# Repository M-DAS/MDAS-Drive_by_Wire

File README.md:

# MDAS-Drive_by_Wire
The drive-by-wire division of the University of Michigan-Dearborn Autonomous Shuttle.

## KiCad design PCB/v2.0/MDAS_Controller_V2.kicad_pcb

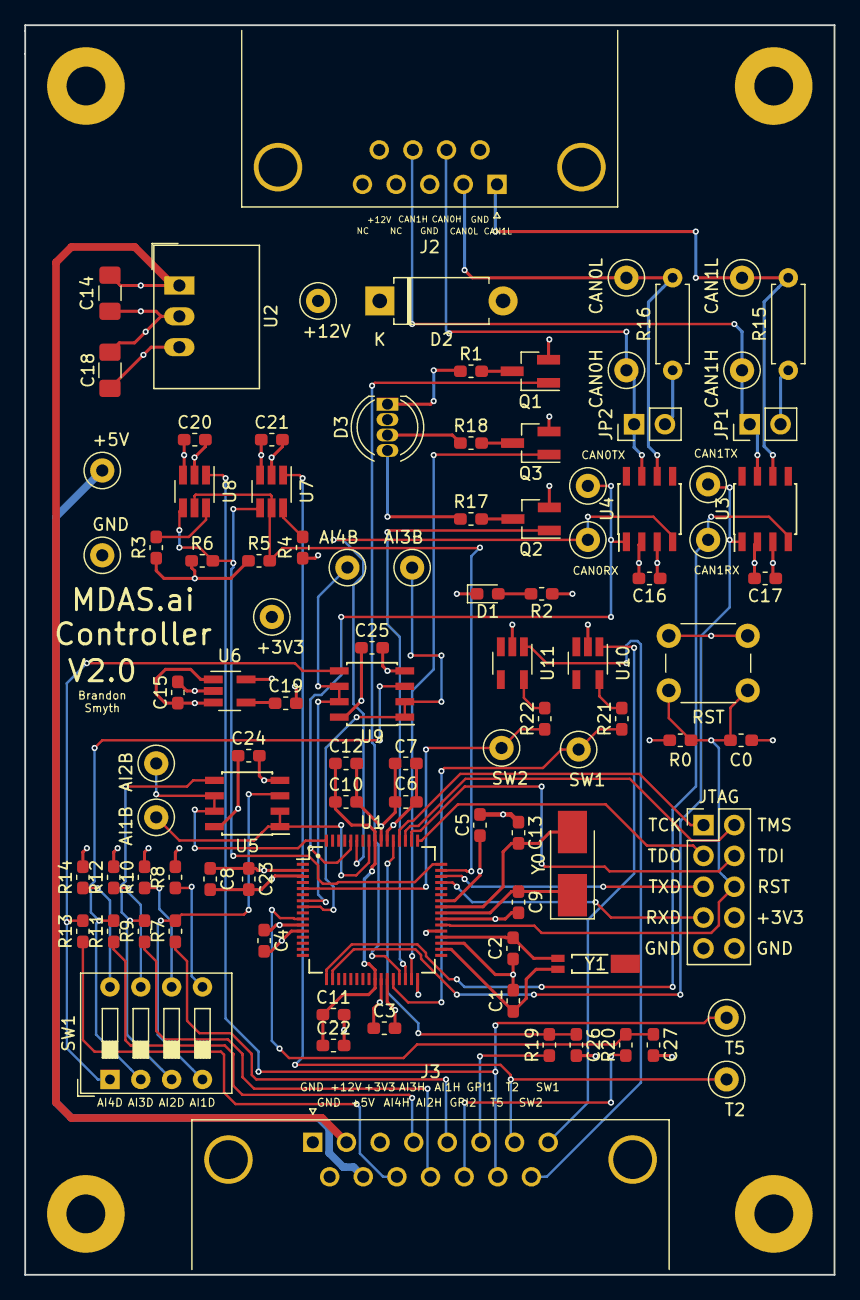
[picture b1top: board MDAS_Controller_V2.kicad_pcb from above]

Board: 4 copper layers, 66.7 x 102.9 mm, 101 parts (0 on the bottom side), 69 nets.

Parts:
+3V3, +5V, +12V: TestPoint; TestPoint_Loop_D1.80mm_Drill1.0mm_Beaded
AI1B, AI2B, AI3B, AI4B: TestPoint; TestPoint_Loop_D1.80mm_Drill1.0mm_Beaded
C0, C3, C4, C5, C6, C10, C11, C16, C17, C20, C21, C24, C25: 0.1uF; C_0603_1608Metric_Pad1.05x0.95mm_HandSolder
C1, C2: 24pF; C_0603_1608Metric_Pad1.05x0.95mm_HandSolder
C7, C22: 2.2uF; C_0603_1608Metric_Pad1.05x0.95mm_HandSolder
C8, C12, C15: 1.0uF; C_0603_1608Metric_Pad1.05x0.95mm_HandSolder
C9, C13: 10pF; C_0603_1608Metric_Pad1.05x0.95mm_HandSolder
C14, C18: 10uF; C_1206_3216Metric_Pad1.42x1.75mm_HandSolder
C19, C23, C26, C27: 0.01uF; C_0603_1608Metric_Pad1.05x0.95mm_HandSolder
CAN0H, CAN0L, CAN0RX, CAN0TX, CAN1H, CAN1L, CAN1RX, CAN1TX: TestPoint; TestPoint_Loop_D1.80mm_Drill1.0mm_Beaded
D1: LED; LED_0603_1608Metric_Pad1.05x0.95mm_HandSolder
D2: TP6KE33A; D_DO-15_P10.16mm_Horizontal
D3: LED_RABG; LED_D5.0mm-4
GND: TestPoint; TestPoint_Loop_D1.80mm_Drill1.0mm_Beaded
J2: DB9_Male; DSUB-9_Male_Horizontal_P2.77x2.84mm_EdgePinOffset9.90mm_Hou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
J3: DB15_Male; DSUB-15_Male_Horizontal_P2.77x2.84mm_EdgePinOffset7.70mm_Ho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
JP1, JP2: Jumper_NC_Small; PinHeader_1x02_P2.54mm_Vertical
JTAG: JTAG; PinHeader_2x05_P2.54mm_Vertical
MH1, MH2, MH3, MH4: MountingHole_Pad; MountingHole_3.2mm_M3_Pad
Q1, Q2, Q3: DTC114E; SOT-23_Handsoldering
R0, R3, R4, R5, R6: 10k; R_0603_1608Metric_Pad1.05x0.95mm_HandSolder
R1, R2, R17, R18: 330; R_0603_1608Metric_Pad1.05x0.95mm_HandSolder
R7, R9, R11, R13: 11k; R_0603_1608Metric_Pad1.05x0.95mm_HandSolder
R8, R10, R12, R14: 21k; R_0603_1608Metric_Pad1.05x0.95mm_HandSolder
R15, R16: 120; R_Axial_DIN0207_L6.3mm_D2.5mm_P7.62mm_Horizontal
R19, R20, R21, R22: 1k; R_0603_1608Metric_Pad1.05x0.95mm_HandSolder
RST: SW_Push; SW_PUSH_6mm_H5mm
SW1: SW_DIP_x04; SW_DIP_SPSTx04_Slide_9.78x12.34mm_W7.62mm_P2.54mm
SW1#2, SW2: TestPoint; TestPoint_Loop_D1.80mm_Drill1.0mm_Beaded
T2, T5: TestPoint; TestPoint_Loop_D1.80mm_Drill1.0mm_Beaded
U1: TM4C123GH6PM; LQFP-64_10x10mm_P0.5mm
U2: R-78E5.0-0.5; Converter_DCDC_RECOM_R-78E-0.5_THT
U3, U4: SN65HVD232; SOIC-8_3.9x4.9mm_P1.27mm
U5, U9: OPA2333xxD; SOIC-8_3.9x4.9mm_P1.27mm
U6: TPS73633DBV; SOT-23-5_HandSoldering
U7, U8: MCP4725A2T-E_CH; SOT-23-6_Handsoldering
U10, U11: TPS70933DBVT; SOT-23-5_HandSoldering
Y0: 16MHz; Crystal_SMD_5032-2Pin_5.0x3.2mm_HandSoldering
Y1: 32.768kHz; ABRACON_AB26TRQ

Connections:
+3V3: +3V3.1, C3.1, C4.1, C5.1, C6.1, C7.1, C8.1, C16.1, C17.1, C23.1, C24.1, C25.1, J3.3, JTAG.8, R0.1, R2.1, U1.2, U1.11, U1.26, U1.37, U1.42, U1.54, U3.3, U4.3, U5.8, U6.5, U9.8
+5V: +5V.1, C15.1, C18.1, C20.1, C21.1, D3.2, J3.10, R3.1, R5.1, R6.1, U2.3, U6.1, U6.3, U7.3, U8.3
+12V: +12V.1, C14.1, D2.1, J2.9, J3.2, U2.1
AI1B: AI1B.1, U1.57, U5.1, U5.2
AI1H: J3.5, R7.1
AI2B: AI2B.1, U1.64, U5.6, U5.7
AI2H: J3.12, R9.1
AI3B: AI3B.1, U1.8, U9.1, U9.2
AI3H: J3.4, R11.1
AI4B: AI4B.1, U1.7, U9.6, U9.7
AI4H: J3.11, R13.1
CAN0H: CAN0H.1, J2.7, JP2.1, U4.7
CAN0L: CAN0L.1, J2.2, R16.2, U4.6
CAN0RX: CAN0RX.1, U1.59, U4.4
CAN0TX: CAN0TX.1, U1.60, U4.1
CAN1H: CAN1H.1, J2.8, JP1.1, U3.7
CAN1L: CAN1L.1, J2.1, R15.2, U3.6
CAN1RX: CAN1RX.1, U1.17, U3.4
CAN1TX: CAN1TX.1, U1.18, U3.1
GND: C0.2, C1.2, C2.2, C3.2, C4.2, C5.2, C6.2, C7.2, C8.2, C9.2, C10.2, C11.2, C12.2, C13.2, C14.2, C15.2, C16.2, C17.2, C18.2, C19.2, C20.2, C21.2, C22.2, C23.2, C24.2, C25.2, C26.2, C27.2, D1.1, D2.2, GND.1, J2.3, J2.6, J3.1, J3.9, JTAG.9, JTAG.10, Q1.2, Q2.2, Q3.2, R4.1, R8.2, R10.2, R12.2, R14.2, RST.1, U1.3, U1.12, U1.27, U1.32, U1.35, U1.39, U1.55, U2.2, U3.2, U4.2, U5.4, U6.2, U7.2, U8.2, U9.4, U10.2, U11.2
GPI1: J3.6, R19.1
GPI2: J3.13, R20.1
LED_B: Q3.1, U1.31
LED_G: Q2.1, U1.30
LED_R: Q1.1, U1.29
unnamed: C1.1, U1.34, Y1.1
unnamed: C2.1, U1.36, Y1.2
unnamed: C9.1, U1.40, Y0.1
unnamed: C10.1, C11.1, C12.1, C22.1, U1.25, U1.56
unnamed: C13.1, U1.41, Y0.2
unnamed: C19.1, U6.4
unnamed: C26.1, R19.2, U1.53
unnamed: C27.1, R20.2, U1.10
unnamed: D1.2, R2.2
unnamed: D3.1, R1.1
unnamed: D3.3, R18.1
unnamed: D3.4, R17.1
unnamed: JP1.2, R15.1
unnamed: JP2.2, R16.1
unnamed: Q1.3, R1.2
unnamed: Q2.3, R17.2
unnamed: Q3.3, R18.2
unnamed: R3.2, U8.6
unnamed: R4.2, U7.6
unnamed: R7.2, SW1.4, U5.3
unnamed: R8.1, SW1.5
unnamed: R9.2, SW1.3, U5.5
unnamed: R10.1, SW1.6
unnamed: R11.2, SW1.2, U9.3
unnamed: R12.1, SW1.7
unnamed: R13.2, SW1.1, U9.5
unnamed: R14.1, SW1.8
unnamed: R21.2, U10.5
unnamed: R22.2, U11.5
RST: C0.1, JTAG.6, R0.2, RST.2, U1.38
RXD: JTAG.7, U1.45
SCL: R5.2, U1.47, U7.5, U8.5
SDA: R6.2, U1.48, U7.4, U8.4
SW1: J3.8, U10.1
SW1P: R21.1, SW1#2.1, U1.28
SW2: J3.15, U11.1
SW2P: R22.1, SW2.1, U1.5
T2: J3.7, T2.1, U7.1
T5: J3.14, T5.1, U8.1
TCK: JTAG.1, U1.52
TDI: JTAG.4, U1.50
TDO: JTAG.3, U1.49
TMS: JTAG.2, U1.51
TXD: JTAG.5, U1.46

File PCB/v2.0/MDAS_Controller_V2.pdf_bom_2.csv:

Component,Description,Part,References,Value,Footprint,Quantity Per PCB,Datasheet,Manufacturer_Name,Arrow Part Number,Height,Arrow Price/Stock,RS Price/Stock,RS Part Number,Manufacturer_Part_Number,Field8,Field4,Field7,Field6,Field5
1,Unpolarized capacitor,C_Small,C19,0.01uF,C_0603_1608Metric_Pad1.05x0.95mm_HandSolder,1,~,,,,,,,,,,,,
2,Unpolarized capacitor,C_Small,C0 C3 C4 C5 C6 C8 C10 C11 C16 C17 C18 C20 C21,0.1uF,C_0603_1608Metric_Pad1.05x0.95mm_HandSolder,13,~,,,,,,,,,,,,
3,Unpolarized capacitor,C_Small,C14,0.33uF,C_0603_1608Metric_Pad1.05x0.95mm_HandSolder,1,~,,,,,,,,,,,,
4,Unpolarized capacitor,C_Small,C7 C12 C15,1.0uF,C_0603_1608Metric_Pad1.05x0.95mm_HandSolder,3,~,,,,,,,,,,,,
5,Unpolarized capacitor,C_Small,C22,2.2uF,C_0603_1608Metric_Pad1.05x0.95mm_HandSolder,1,~,,,,,,,,,,,,
6,Unpolarized capacitor,C_Small,C1 C2 C9 C13,24pF,C_0603_1608Metric_Pad1.05x0.95mm_HandSolder,4,~,,,,,,,,,,,,
7,LED generic,LED,D1,LED,LED_0603_1608Metric_Pad1.05x0.95mm_HandSolder,1,~,,,,,,,,,,,,
8,"1500W unidirectional TRANSZORB® Transient Voltage Suppressor, DO-201AE",1.5KExxA,D2,TP6KE33A,D_DO-201AE_P12.70mm_Horizontal,1,https://www.vishay.com/docs/88301/15ke.pdf,,,,,,,,,,,,
9,150mA 30V Ultra-Low-Iq Wide-Input Low-Dropout (LDO) Regulator With Reverse Current Protection,TPS70933DBVT,IC1 IC2,TPS70933DBVT,SOT-23-5_HandSoldering,2,http://www.ti.com/lit/gpn/tps709,Texas Instruments,TPS70933DBVT,1.45,https://www.arrow.com/en/products/tps70933dbvt/texas-instruments,http://uk.rs-online.com/web/p/products/8257033P,8257033P,TPS70933DBVT,,,,,
10,15-pin female D-SUB connector (low-density/2 columns),DB15_Female,J5,DB15_Female,DSUB-15_Female_Horizontal_P2.77x2.54mm_EdgePinOffset9.40mm,1, ~,,,,,,,,,,,,
11,9-pin male D-SUB connector,DB9_Male,J2,DB9_Male,DSUB-9_Male_Horizontal_P2.77x2.54mm_EdgePinOffset9.40mm,1, ~,,,,,,,,,,,,
12,"Generic connector, double row, 02x05, top/bottom pin numbering scheme (row 1: 1...pins_per_row, row2: pins_per_row+1 ... num_pins), script generated (kicad-library-utils/schlib/autogen/connector/)",Conn_02x05_Top_Bottom,J1,JTAG,PinHeader_2x05_P2.54mm_Vertical,1,~,,,,,,,,,,,,
13,"Jumper, normally closed",Jumper_NC_Small,JP1 JP2,Jumper_NC_Small,PinHeader_1x02_P2.54mm_Vertical,2,~,,,,,,,,,,,,
14,Resistor,R,R1,0,R_0603_1608Metric_Pad1.05x0.95mm_HandSolder,1,~,,,,,,,,,,,,
15,Resistor,R,R0 R3 R4 R5 R6,10k,R_0603_1608Metric_Pad1.05x0.95mm_HandSolder,5,~,,,,,,,,,,,,
16,Resistor,R,R7 R9 R11 R13,11k,R_0603_1608Metric_Pad1.05x0.95mm_HandSolder,4,~,,,,,,,,,,,,
17,Resistor,R,R15 R16,120,R_Axial_DIN0207_L6.3mm_D2.5mm_P7.62mm_Horizontal,2,~,,,,,,,,,,,,
18,Resistor,R,R8 R10 R12 R14,21k,R_0603_1608Metric_Pad1.05x0.95mm_HandSolder,4,~,,,,,,,,,,,,
19,Resistor,R,R2,330,R_0603_1608Metric_Pad1.05x0.95mm_HandSolder,1,~,,,,,,,,,,,,
20,"Push button switch, generic, two pins",SW_Push,SW0,SW_Push,SW_SPST_TL3305B,1,,,,,,,,,,,,,
21,,MCP4725A2T-E_CH,U7 U8,MCP4725A2T-E_CH,SOT-23-6_Handsoldering,2,Microchip,,,,,,,,Unavailable,SOT-23-6 Microchip,MCP4725A2T-E/CH,None,MCP4725 Series 1 Ch I2C EEPROM Memory 5.5 V 12-Bit D/A Converter SMT - SOT-23-6
22,"Dual 1.8V, microPower, CMOS Operational Amplifiers, Zero-Drift Series, SOIC-8",OPA2333xxD,U5 U9,OPA2333xxD,SOIC-8_3.9x4.9mm_P1.27mm,2,http://www.ti.com/lit/ds/symlink/opa333.pdf,,,,,,,,,,,,
23,"500mA Step-Down DC/DC-Regulator, 7-28V input, 5V fixed Output Voltage, LM78xx replacement, -40°C to +85°C, SIP3",R-78E5.0-0.5,U2,R-78E5.0-0.5,Converter_DCDC_RECOM_R-78E-0.5_THT,1,https://www.recom-power.com/pdf/Innoline/R-78Exx-0.5.pdf,,,,,,,,,,,,
24,"CAN Bus Transceivers, 3.3V, 1Mbps, SOIC",SN65HVD232,U3 U4,SN65HVD232,SOIC-8_3.9x4.9mm_P1.27mm,2,http://www.ti.com/lit/ds/symlink/sn65hvd230.pdf,,,,,,,,,,,,
25,"Tiva ARM 32bit CortexM4 Microcotroller, 80MHz, 256kB Flash, 32kB SRAM, 2k EEPROM, LQFP64",TM4C123GH6PM,U1,TM4C123GH6PM,LQFP-64_10x10mm_P0.5mm,1,http://www.ti.com/lit/ds/symlink/tm4c123gh6pm.pdf,,,,,,,,,,,,
26,"Cap free NMOS 400mA Low Drop 3.3V Regulator, SOT-23-5",TPS73633DBV,U6,TPS73633DBV,SOT-23-5_HandSoldering,1,http://www.ti.com/lit/ds/symlink/tps736.pdf,,,,,,,,,,,,
27,Two pin crystal,Crystal,Y0,16MHz,Crystal_SMD_Abracon_ABM3-2Pin_5.0x3.2mm_HandSoldering,1,~,,,,,,,,,,,,
28,Two pin crystal,Crystal,Y1,32.768kHz,ABRACON_AB26TRQ,1,~,,,,,,,,,,,,





Component Groups:,28
Component Count:,61
Fitted Components:,61
Number of PCBs:,1
Total components:,61
Schematic Version:,2
Schematic Date:,2018-08-24
BoM Date:,8/25/2018 5:22:28 PM
Schematic Source:,C:\Users\Brandon Smyth\Desktop\MDAS_Controller_V2\MDAS_Controller_V2.sch
KiCad Version:,Eeschema (5.0.0)

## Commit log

2018-05-08 Create Hi
2018-05-08 Create pretend code
    code to annoy Ethan with
2018-05-08 Added Noah's files
2018-05-08 Folder or the braking actuator
2018-05-08 Steering Actuator files
2018-05-08 changed folder name
2018-05-25 test to annoy Ethan
2018-06-12 Changes to Steering Actuation
    Took the derivative between two torques and established a torque threshold based on the result. If the threshold was passed, it would change to a state that would keep the position of the wheels and 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
2018-07-09 My code after like 28 Days
    Steering stuff
2018-07-10 Added dac.c skeleton
    Missing scaling function. Will need scaling equation from throttle voltage range.
2018-07-10 Throttle Main Written
    Throttle Main has been written to the point that I only need the "write to DAC" functions and it''ll be good to be programmed.
2018-07-10 Fixed Typo
    Fixed typo << 1 vs << 2
2018-07-11 Changed Masking Logic
    Reversed logic from last iteration to only update data when the ID is found.
2018-07-23 Added DAC LUT
2018-07-23 Added dac.h
2018-07-23 Some throttle stuff
    The stuff I contributed to the main so that I can get Ben's baller helper function code.
2018-07-23 More throttle stuff
    I forgot to save it
2018-07-28 Finalized ADC, DAC functions
    ADC to percent still needs to be scaled to percent. Equation is currently missing. Drive_by_Wire.c will need to be updated to reflect DAC instead of digital potentiometers.
2018-07-30 Main Logic (7/29)
    Shouldn't include merge conflicts.
2018-07-30 Main Changes
    Minor Changes to Main since last commit.
2018-07-30 added v1.0 PCB files
2018-07-30 Fixed ADC input scaling
    Scaled ADC input to 0-100 percent
2018-07-31 Reupload Pedal_ADC.c
2018-07-31 Changes from 7-31-2018
    It compiled I promise.
2018-08-01 Reading over CAN
    Reads in messages over CAN and is now able to change states. As far as hardware goes, PCB has bad wire connection. Please remember to check.
2018-08-22 Current vehicle code
2018-08-22 PCB changes
2018-09-07 Add V2 Board to Repo
2018-09-23 Redesign routing
2018-09-26 Minor changes before Hughes manufactures
